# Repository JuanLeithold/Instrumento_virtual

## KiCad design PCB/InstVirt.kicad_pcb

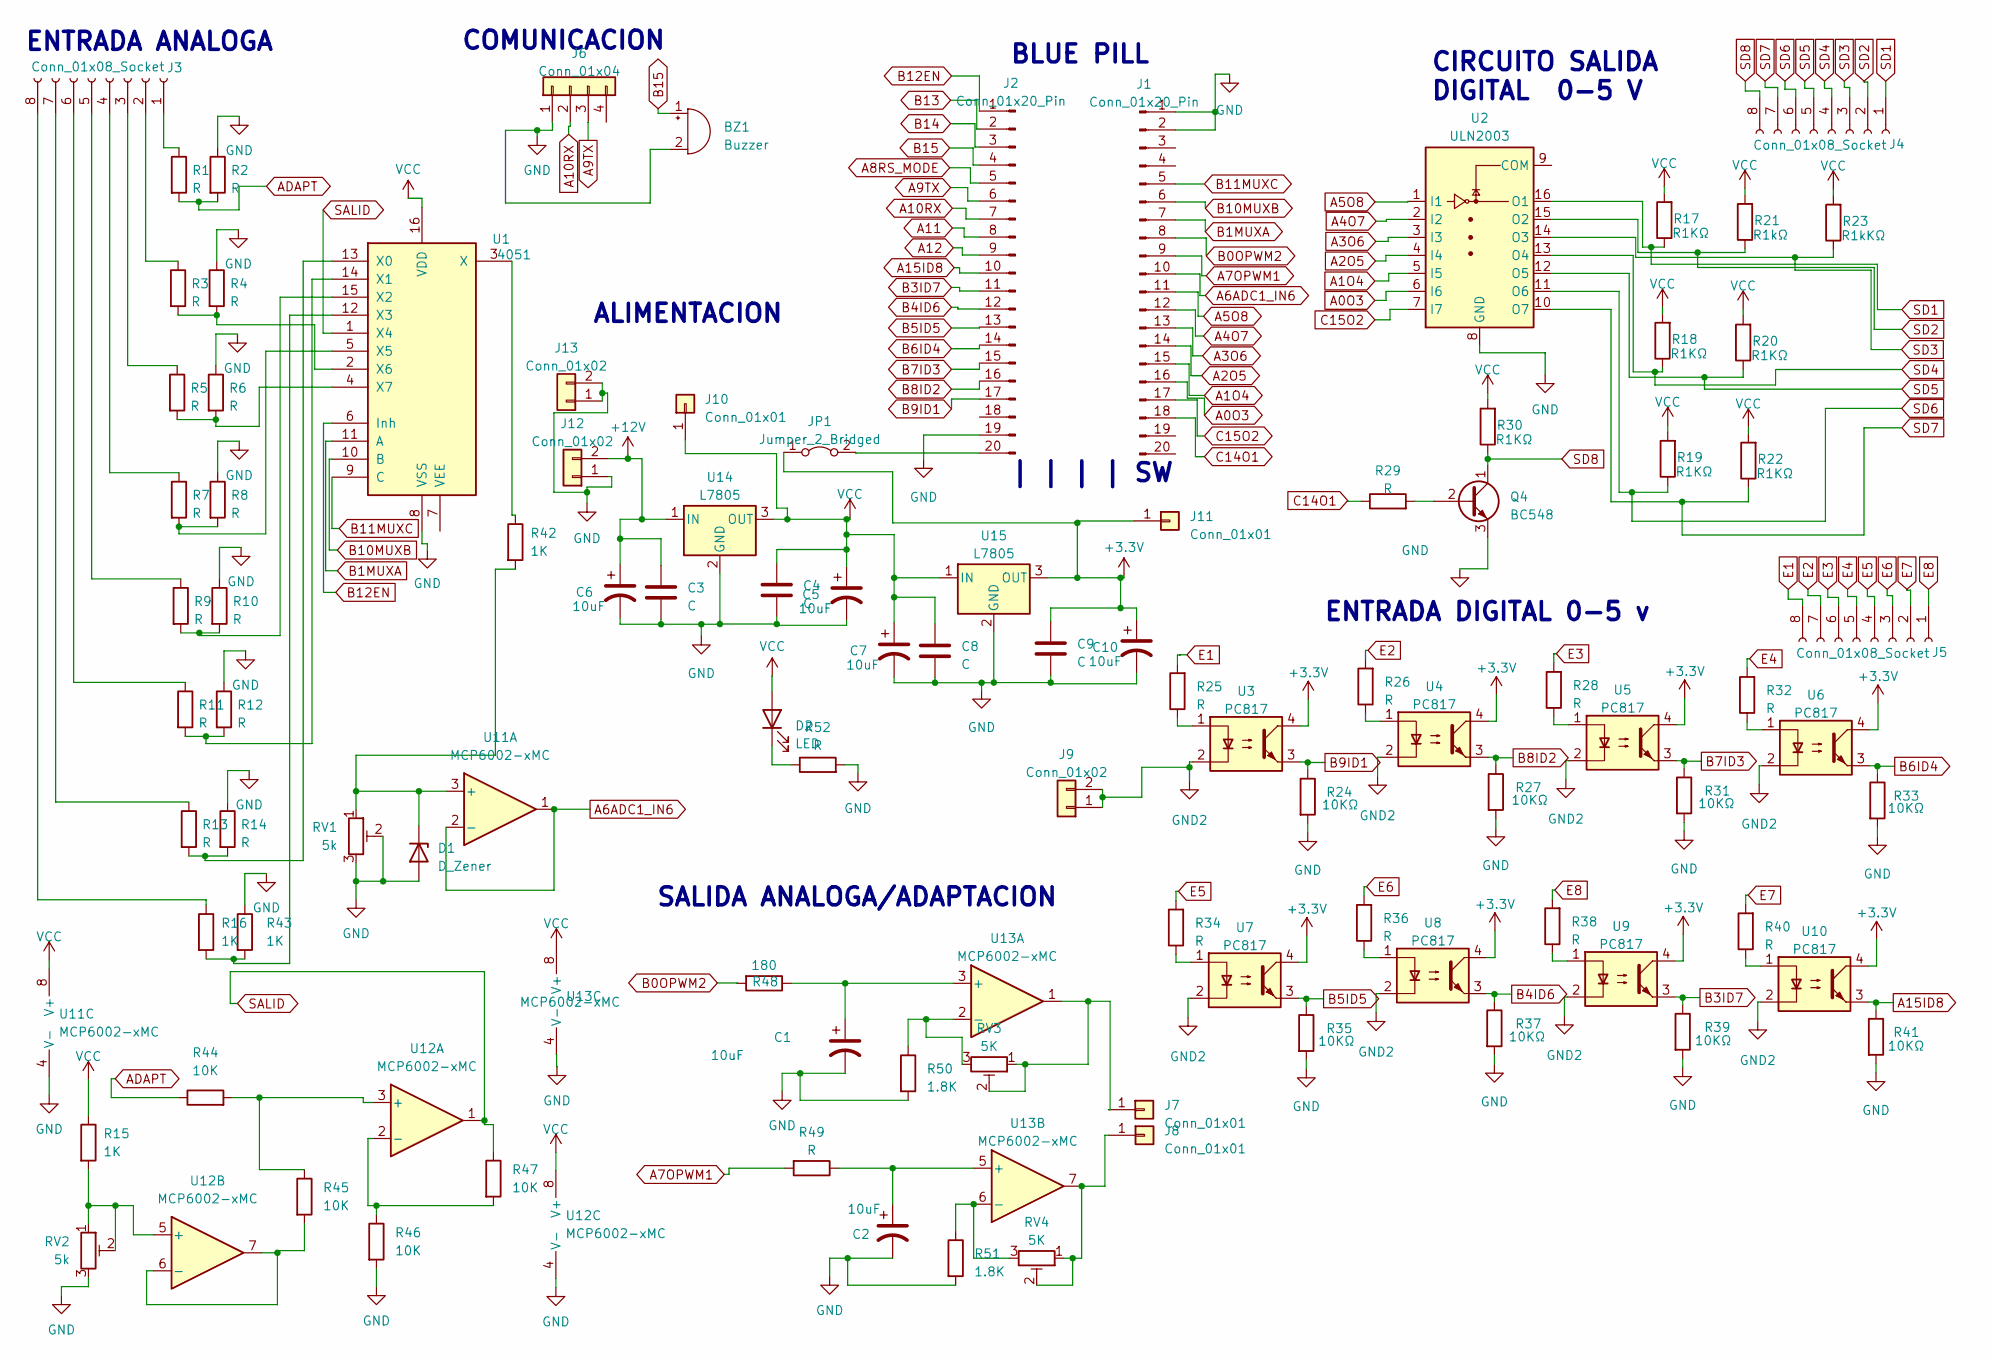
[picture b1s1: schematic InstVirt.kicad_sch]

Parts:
BZ1: Buzzer; MagneticBuzzer_ProSignal_ABI-010-RC
C1, C2, C5, C6, C7, C10: 10uF; CP_Radial_D5.0mm_P2.50mm
C3, C4, C8, C9: C; C_Disc_D5.0mm_W2.5mm_P5.00mm
D1: D_Zener; D_DO-34_SOD68_P10.16mm_Horizontal
D2: LED; LED_D5.0mm
J1, J2: Conn_01x20_Pin; PinSocket_1x20_P2.54mm_Vertical
J3, J5: Conn_01x08_Socket; PinHeader_1x08_P2.54mm_Vertical
J4: Conn_01x08_Socket; PinSocket_1x08_P2.54mm_Vertical
J6: Conn_01x04; PinSocket_1x04_P2.54mm_Vertical
J7, J8, J10, J11: Conn_01x01; PinSocket_1x01_P2.54mm_Vertical
J9: Conn_01x02; PinSocket_1x02_P2.54mm_Vertical
J12, J13: Conn_01x02; TerminalBlock_Phoenix_MKDS-1,5-2_1x02_P5.00mm_Horizontal
JP1: Jumper_2_Bridged; PinSocket_1x02_P2.54mm_Vertical
Q4: BC548; TO-92_Inline
R1, R3, R5, R7, R9, R11, R13, R49: R; R_1206_3216Metric
R2, R4, R6, R8, R10, R12, R14, R25, R26, R28, R29, R32, R34, R36, R38, R40, R52: R; R_Axial_DIN0207_L6.3mm_D2.5mm_P10.16mm_Horizontal
R15, R16, R42: 1K; R_1206_3216Metric
R17, R18, R19, R20, R22, R30: R1KΩ; R_1206_3216Metric
R21: R1kΩ; R_1206_3216Metric
R23: R1kKΩ; R_1206_3216Metric
R24, R27, R31, R33, R35, R37, R39, R41: 10KΩ; R_1206_3216Metric
R43: 1K; R_Axial_DIN0207_L6.3mm_D2.5mm_P10.16mm_Horizontal
R44, R45, R46, R47: 10K; R_1206_3216Metric
R48: 180; R_1206_3216Metric
R50, R51: 1.8K; R_Axial_DIN0207_L6.3mm_D2.5mm_P10.16mm_Horizontal
RV1, RV2: 5k; Potentiometer_Bourns_3296W_Vertical
RV3, RV4: 5K; Potentiometer_Bourns_3296W_Vertical
U1: 4051; DIP-16_W7.62mm_LongPads
U2: ULN2003; SOP-16_4.4x10.4mm_P1.27mm
U3, U4, U5, U6, U7, U8, U9, U10: PC817; DIP-4_W7.62mm
U11, U12, U13: MCP6002-xMC; DIP-8_W7.62mm_LongPads
U14, U15: L7805; TO-220-3_Vertical

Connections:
+3.3V: C9.1, C10.1, J11.1, JP1.1 (A), U3.4, U4.4, U5.4, U6.4, U7.4, U8.4, U9.4, U10.4, U15.3 (OUT)
+12V: C3.1, C6.1, J12.2, U14.1 (IN)
A0O3: J1.16, U2.6 (I6)
A1O4: J1.15, U2.5 (I5)
A2O5: J1.14, U2.4 (I4)
A3O6: J1.13, U2.3 (I3)
A4O7: J1.12, U2.2 (I2)
A5O8: J1.11, U2.1 (I1)
A6ADC1_IN6: J1.10, U11.1, U11.2 (-)
A7OPWM1: J1.9, R49.2
A8RS_MODE: J2.5
A9TX: J2.6, J6.3
A10RX: J2.7, J6.2
A11: J2.8
A12: J2.9
A15ID8: J2.10, R41.1, U10.3
ADAPT: R1.2, R2.2, R44.1
B0OPWM2: J1.8, R48.2
B1MUXA: J1.7, U1.11 (A)
B3ID7: J2.11, R39.1, U9.3
B4ID6: J2.12, R37.1, U8.3
B5ID5: J2.13, R35.1, U7.3
B6ID4: J2.14, R33.1, U6.3
B7ID3: J2.15, R31.1, U5.3
B8ID2: J2.16, R27.1, U4.3
B9ID1: J2.17, R24.1, U3.3
B10MUXB: J1.6, U1.10 (B)
B11MUXC: J1.5, U1.9 (C)
B12EN: J2.1, U1.6 (Inh)
B13: J2.2
B14: J2.3
B15: BZ1.1 (-), J2.4
C14O1: J1.18, R29.1
C15O2: J1.17, U2.7 (I7)
E1: J5.8, R25.2
E2: J5.7, R26.2
E3: J5.6, R28.2
E4: J5.5, R32.2
E5: J5.4, R34.2
E6: J5.3, R36.2
E7: J5.2, R40.2
E8: J5.1, R38.2
GND: BZ1.2 (+), C1.2, C2.2, C3.2, C4.2, C5.2, C6.2, C7.2, C8.2, C9.2, C10.2, D1.2 (A), J1.1, J1.2, J2.19, J6.1, J12.1, J13.1, J13.2, Q4.3 (E), R2.1, R4.1, R6.1, R8.1, R10.1, R12.1, R14.1, R24.2, R27.2, R31.2, R33.2, R35.2, R37.2, R39.2, R41.2, R43.1, R46.2, R50.2, R51.2, R52.2, RV1.2, RV1.3, RV2.3, U1.8 (VSS), U2.8 (GND), U11.4 (V-), U11.9 (V-), U12.4 (V-), U12.9 (V-), U13.4 (V-), U13.9 (V-), U14.2 (GND), U15.2 (GND)
GND2: J9.1, J9.2, U3.2, U4.2, U5.2, U6.2, U7.2, U8.2, U9.2, U10.2
unnamed: D1.1 (K), R42.2, RV1.1, U11.3 (+)
unnamed: D2.1 (K), R52.1
unnamed: J2.20, JP1.2 (B)
unnamed: J3.1, R1.1
unnamed: J3.2, R3.1
unnamed: J3.3, R5.1
unnamed: J3.4, R7.1
unnamed: J3.5, R9.1
unnamed: J3.6, R11.1
unnamed: J3.7, R13.1
unnamed: J3.8, R16.1
unnamed: J7.1, RV3.1, RV3.2, U13.1
unnamed: J8.1, RV4.1, RV4.2, U13.7
unnamed: Q4.2 (B), R29.2
unnamed: R25.1, U3.1
unnamed: R26.1, U4.1
unnamed: R28.1, U5.1
unnamed: R32.1, U6.1
unnamed: R34.1, U7.1
unnamed: R36.1, U8.1
unnamed: R38.1, U9.1
unnamed: R40.1, U10.1
unnamed: R13.2, R14.2, U1.13 (X0)
unnamed: R11.2, R12.2, U1.14 (X1)
unnamed: R9.2, R10.2, U1.15 (X2)
unnamed: R16.2, R43.2, U1.12 (X3)
unnamed: R7.2, R8.2, U1.5 (X5)
unnamed: R3.2, R4.2, U1.2 (X6)
unnamed: R5.2, R6.2, U1.4 (X7)
unnamed: R42.1, U1.3 (X)
unnamed: R44.2, R45.1, U12.3 (+)
unnamed: R46.1, R47.2, U12.2 (-)
unnamed: R15.2, RV2.1, RV2.2, U12.5 (+)
unnamed: R45.2, U12.6 (-), U12.7
unnamed: C1.1, R48.1, U13.3 (+)
unnamed: R50.1, RV3.3, U13.2 (-)
unnamed: C2.1, R49.1, U13.5 (+)
unnamed: R51.1, RV4.3, U13.6 (-)
SALID: R47.1, U1.1 (X4), U12.1
SD1: J4.1, R17.1, U2.16 (O1)
SD2: J4.2, R21.1, U2.15 (O2)
SD3: J4.3, R23.1, U2.14 (O3)
SD4: J4.4, R18.1, U2.13 (O4)
SD5: J4.5, R20.1, U2.12 (O5)
SD6: J4.6, R19.1, U2.11 (O6)
SD7: J4.7, R22.1, U2.10 (O7)
SD8: J4.8, Q4.1 (C), R30.1
VCC: C4.1, C5.1, C7.1, C8.1, D2.2 (A), J10.1, R15.1, R17.2, R18.2, R19.2, R20.2, R21.2, R22.2, R23.2, R30.2, U1.16 (VDD), U11.8 (V+), U12.8 (V+), U13.8 (V+), U14.3 (OUT), U15.1 (IN)

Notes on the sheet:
CIRCUITO SALIDA DIGITAL 0-5 V
BLUE PILL
ENTRADA ANALOGA
COMUNICACION
ENTRADA DIGITAL 0-5 v
| | | | SW
SALIDA ANALOGA/ADAPTACION
ALIMENTACION

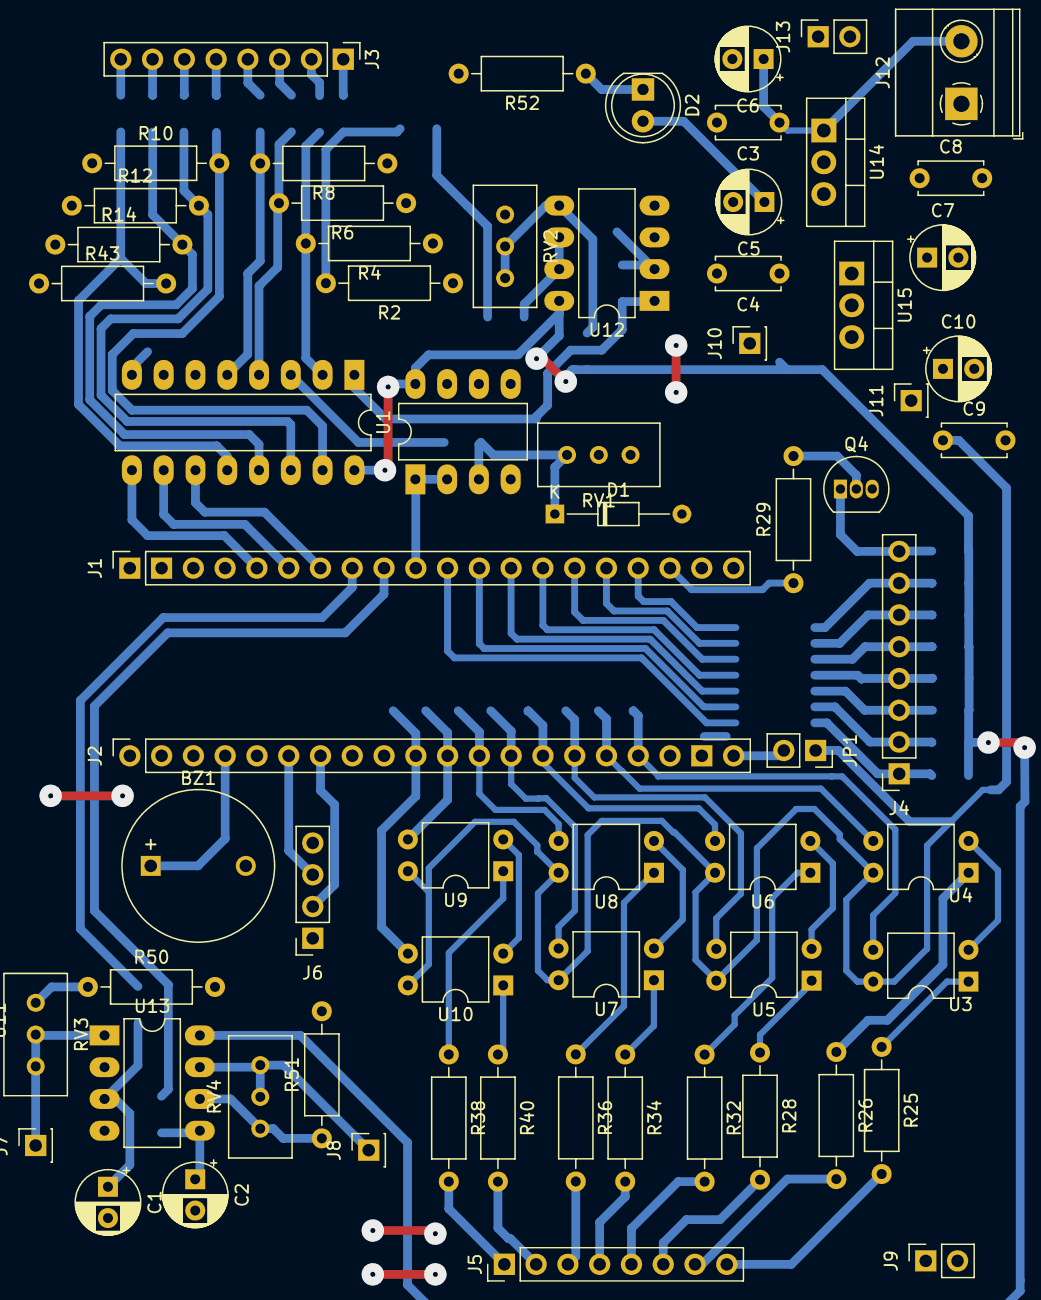
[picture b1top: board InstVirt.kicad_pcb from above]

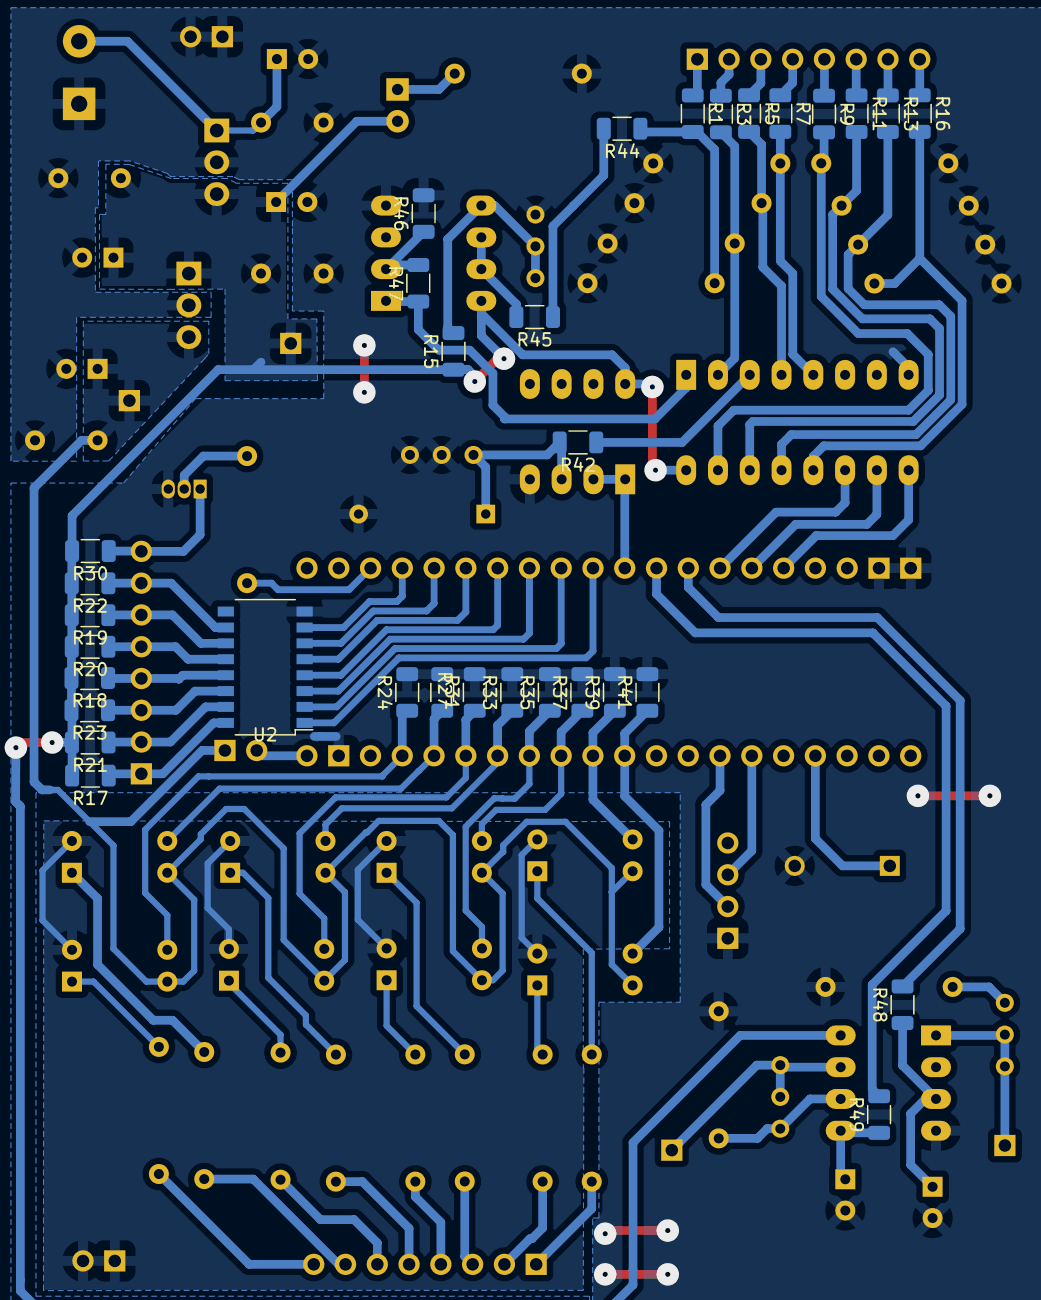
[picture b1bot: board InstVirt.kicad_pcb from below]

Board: 2 copper layers, 99 parts (33 on the bottom side), 87 nets.

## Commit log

2023-09-29 Primera version de comunicación RS485. No funcional
2023-10-02 Primera version de comunicacion: Se envia un dato por real term y se prende el led de la bluepill
2023-10-02 Transmision de datos a realterm
2023-10-02 Tx y rx con realterm ok
2023-10-06 Se agrega codigo de QT. Se logra comunicacion tx y rx entre ambos y control de datos
2023-10-06 Cambio de nombre del proyecto
2023-10-06 Delete Prueba_rs485 directory
    Elimino carpeta con el nombre del proyecto viejo
2023-10-06 Se configura proyecto para que tenga nombre de directorio y de archivo adecuado
2023-10-06 Cambio del nombre de archivo y proyecto
2023-10-06 Prueba subida Juan
2023-10-10 Funciona PWM Variable co QT. Se comienza separacion de archivos
2023-10-12 Se agregan dos funciones de timer con PWM en funcionamiento. Se acomodan archivos de QT para mejor compresion
2023-10-12 Se agrega thread funcional como ejemplo
2023-10-14 prueba jose
2023-10-14 borre hola.txt
2023-10-16 Agrege la carpeta de pcb
2023-10-17 Actualizo circuito PCB
2023-10-18 actualizacion pcb2
2023-10-19 Se consigue arreglo para enviar por puerto serie
2023-10-20 ADC CON TIMER
2023-10-21 Bluepill con manejo de datos para el adc
2023-10-21 Se agrega clase de thread en QT
2023-10-21 cambio en el adc_timer
2023-10-21 cambios
2023-10-21 actualizacion pcb3
2023-10-21 actualizacion Bluepillpinout
2023-10-21 Cambio2
2023-10-22 cambios3
2023-10-22 cambios4
2023-10-25 Comunicacion Tx en BP y Rx en QT con estructura. Interfaz QT Ok.
2023-10-28 Funciona comunicacion bluepill e interfaz
2023-11-03 SUBIDA DE PDF
2023-11-03 Actualizacion codigo BPill
2023-11-04 Actualizacion codigo BPill nueva
2023-11-10 se implementa boton de encendido y apagado en QT
2023-11-11 archivos que faltaron
2023-11-15 actualizacion pcb4
2023-11-16 actualizacion pcb5
2023-11-20 ADC en blue pill y actualizacion en QT
2023-11-20 ADC, cambio de patas en el mux
2023-11-24 Solo faltan entradas analóogicas
